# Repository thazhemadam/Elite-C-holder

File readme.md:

# splinterface

splinterface is an MCU holder, intended for use in both standalone and split builds.

## MCU Support

The following footprints are supported by the holder.

* [Elite-C footprint](https://deskthority.net/wiki/Elite-C)
* [nice!nano footprint](https://nicekeyboards.com/docs/nice-nano/pinout-schematic/#pinout)
* [Supermini nrf52840 footprint](https://github.com/joric/nrfmicro/wiki/Alternatives#supermini-nrf52840)

## Features

* [VIK](https://github.com/sadekbaroudi/vik) compliant
* Support for wireless and wired builds (see an example compatibility matrix [below](#compatibility-matrix-with-bastardkb-boards))
* Full-duplex communications support
* Dedicated pin for handedness (optional)
* Dedicated pin for RGB (optional)
* Criss-crossable pins for serial communication

### Wired Builds

* TRRS jack for split communications
* USBLC6-2P6 for ESD protection

### Wireless Builds

* JST-PH connector for connecting a battery
* EG1271 Slide Switches for power switch

## Compatibility Matrix with BastardKB Boards

|                | RGB | Wireless | RGB + Wireless [^1] |
|----------------|:---:|:--------:|:-------------------:|
| Skeletyl       | ✅   | ✅        | ✅                 |
| Charybdis Nano | ✅   | ✅        | ✅                 |
| TBK Mini       | ✅   | ✅ [^2]   | ✅ [^2][^3]        |
| Charybdis Mini | ✅   | ✅ [^2]   | ✅ [^2][^3]        |
| Scylla         | ✅   | ✅ [^3]   | ❌                 |
| Charybdis      | ✅   | ✅ [^3]   | ❌                 |

* Ribbon cable pinout (for the key matrix) compatible with BastardKB's [Dactyl](https://bastardkb.com/dactyls/) and [Charybdis](https://bastardkb.com/charybdis/) series' PCBs.
* Mounting holes are compatible with BastardKB's [Dactyl](https://bastardkb.com/dactyls/) and [Charybdis](https://bastardkb.com/charybdis/) series' cases.

## VIK Certification Card

| Category                | Response           |
| ----------------------- |:------------------:|
| FPC connector           | ✅                 |
| Breakout pins           | ❌                 |
| Supplies: SPI           | ✅                 |
| Supplies: I2C           | ✅                 |
| I2C on main PCB         | ❌                 |
| I2C pull ups            | N/A                |
| Supplies: RGB           | ✅                 |
| Supplies: Extra GPIO 1  | Analog/Digital     |
| Supplies: Extra GPIO 2  | Analog/Digital     |

## License

This work is licensed under a Creative Commons Attribution-NonCommercial-ShareAlike 4.0 International License.

[^1]: Do you even really want to have RGB with a wireless build? Do you, *really*? For obvious battery-related reasons, this is not a recommended build configuration.
[^2]: Requires the `RGB_OR_WL_COL` jumper to be manually soldered appropriately.
[^3]: Requires the `split_hand_or_row` jumper to be manually soldered appropriately. This will reappropriate the dedicated handedness pin. In this case, the handedness will have to be defined in the firmware.

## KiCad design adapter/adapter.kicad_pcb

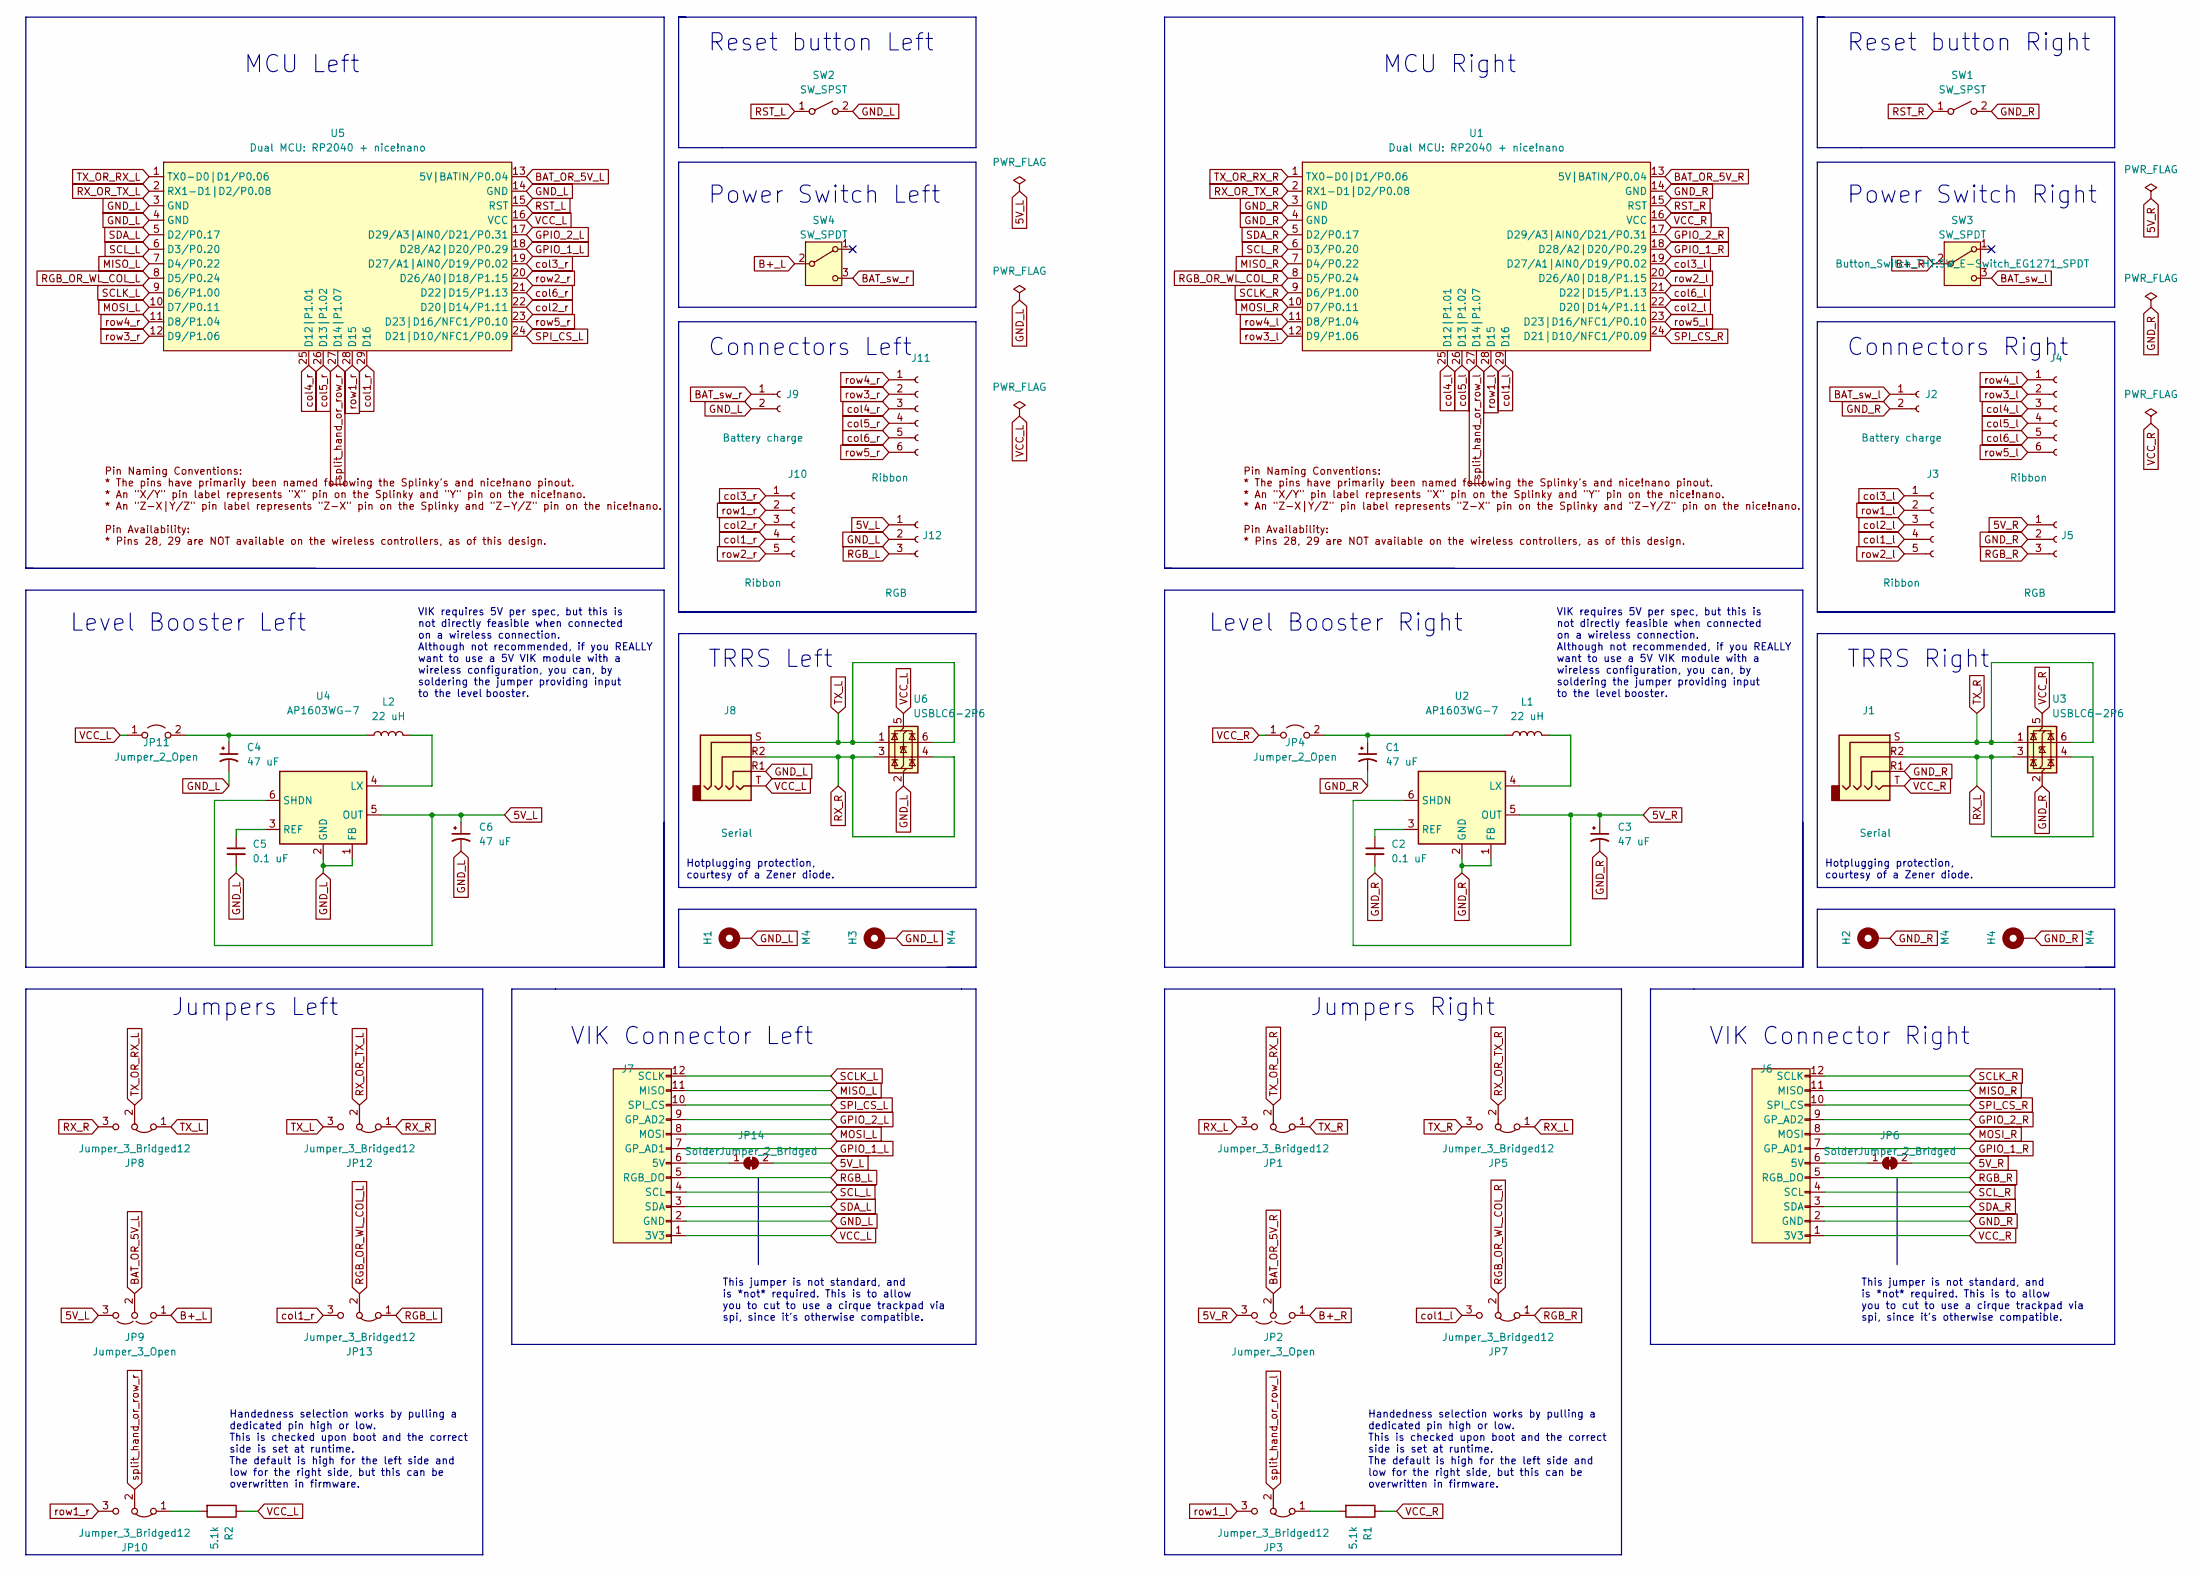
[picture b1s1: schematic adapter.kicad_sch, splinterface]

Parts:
C1, C3, C4, C6: 47 uF; C_0805_2012Metric; LCSC C140782
C2, C5: 0.1 uF; C_0805_2012Metric; LCSC C1525
H1, H2, H3, H4: M4; MountingHole_4mm_Pad_thin
J1, J8: Serial; CON_MJ-4PP-9
J2, J9: Battery charge; JST_PH_B2B-PH-K_1x02_P2.00mm_Vertical
J3, J10: Ribbon; 5_PinHeader
J4, J11: Ribbon; 6_PinHeader
J5, J12: RGB; header1x03
J6, J7: vik-keyboard-connector-horizontal; LCSC C479750
JP1, JP3, JP5, JP7, JP8, JP10, JP12, JP13: Jumper_3_Bridged12; SolderJumper-3_P1.3mm_Bridged12_RoundedPad1.0x1.5mm
JP2, JP9: Jumper_3_Open; SolderJumper-3_P1.3mm_Open_RoundedPad1.0x1.5mm_NumberLabels
JP4, JP11: Jumper_2_Open; SolderJumper-2_P1.3mm_Open_RoundedPad1.0x1.5mm
JP6, JP14: SolderJumper_2_Bridged; SolderJumper-2_P1.3mm_Bridged_RoundedPad1.0x1.5mm
L1, L2: 22 uH; L_0805_2012Metric; LCSC C361669
R1, R2: 5.1k; R_1206_handsolder; JLCPCB BOM 1
SW1, SW2: SW_SPST; PushSwitch
SW3, SW4: SW_SPDT; SW_E-Switch_EG1271_SPDT
U1, U5: Dual MCU: RP2040 + nice!nano; Dual-MCU-rp2040-nice-nano
U2, U4: AP1603WG-7; SOT-23-6; LCSC C192712
U3, U6: USBLC6-2P6; SOT-23-6

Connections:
5V_L: C6.1, J12.1, JP9.3 (B), JP14.2 (B), U4.5 (OUT), U4.6 (SHDN)
5V_R: C3.1, J5.1, JP2.3 (B), JP6.2 (B), U2.5 (OUT), U2.6 (SHDN)
B+_L: JP9.1 (A), SW4.2 (B)
B+_R: JP2.1 (A), SW3.2 (B)
BAT_OR_5V_L: JP9.2 (C), U5.13 (5V|BATIN/P0.04)
BAT_OR_5V_R: JP2.2 (C), U1.13 (5V|BATIN/P0.04)
BAT_sw_l: J2.1, SW3.3 (C)
BAT_sw_r: J9.1, SW4.3 (C)
GND_L: C4.2, C5.2, C6.2, H1.1, H3.1, J7.2 (GND), J8.R1, J9.2, J12.2, SW2.2 (B), U4.1 (FB), U4.2 (GND), U5.3 (GND), U5.4 (GND), U5.14 (GND), U6.2 (GND)
GND_R: C1.2, C2.2, C3.2, H2.1, H4.1, J1.R1, J2.2, J5.2, J6.2 (GND), SW1.2 (B), U1.3 (GND), U1.4 (GND), U1.14 (GND), U2.1 (FB), U2.2 (GND), U3.2 (GND)
GPIO_1_L: J7.7 (GP_AD1), U5.18 (D28/A2|D20/P0.29)
GPIO_1_R: J6.7 (GP_AD1), U1.18 (D28/A2|D20/P0.29)
GPIO_2_L: J7.9 (GP_AD2), U5.17 (D29/A3|AIN0/D21/P0.31)
GPIO_2_R: J6.9 (GP_AD2), U1.17 (D29/A3|AIN0/D21/P0.31)
MISO_L: J7.11 (MISO), U5.7 (D4/P0.22)
MISO_R: J6.11 (MISO), U1.7 (D4/P0.22)
MOSI_L: J7.8 (MOSI), U5.10 (D7/P0.11)
MOSI_R: J6.8 (MOSI), U1.10 (D7/P0.11)
unnamed: J6.6 (5V), JP6.1 (A)
unnamed: J7.6 (5V), JP14.1 (A)
unnamed: JP3.1 (A), R1.2
unnamed: C1.1, JP4.2 (B), L1.1
unnamed: JP10.1 (A), R2.2
unnamed: C4.1, JP11.2 (B), L2.1
unnamed: L1.2, U2.4 (LX)
unnamed: C2.1, U2.3 (REF)
unnamed: L2.2, U4.4 (LX)
unnamed: C5.1, U4.3 (REF)
RGB_L: J7.5 (RGB_DO), J12.3, JP13.1 (A)
RGB_OR_WL_COL_L: JP13.2 (C), U5.8 (D5/P0.24)
RGB_OR_WL_COL_R: JP7.2 (C), U1.8 (D5/P0.24)
RGB_R: J5.3, J6.5 (RGB_DO), JP7.1 (A)
RST_L: SW2.1 (A), U5.15 (RST)
RST_R: SW1.1 (A), U1.15 (RST)
RX_L: J1.R2, JP1.3 (B), JP5.1 (A), U3.3 (I/O2), U3.4 (I/O2)
RX_OR_TX_L: JP12.2 (C), U5.2 (RX1-D1|D2/P0.08)
RX_OR_TX_R: JP5.2 (C), U1.2 (RX1-D1|D2/P0.08)
RX_R: J8.R2, JP8.3 (B), JP12.1 (A), U6.3 (I/O2), U6.4 (I/O2)
SCLK_L: J7.12 (SCLK), U5.9 (D6/P1.00)
SCLK_R: J6.12 (SCLK), U1.9 (D6/P1.00)
SCL_L: J7.4 (SCL), U5.6 (D3/P0.20)
SCL_R: J6.4 (SCL), U1.6 (D3/P0.20)
SDA_L: J7.3 (SDA), U5.5 (D2/P0.17)
SDA_R: J6.3 (SDA), U1.5 (D2/P0.17)
SPI_CS_L: J7.10 (SPI_CS), U5.24 (D21|D10/NFC1/P0.09)
SPI_CS_R: J6.10 (SPI_CS), U1.24 (D21|D10/NFC1/P0.09)
TX_L: J8.S, JP8.1 (A), JP12.3 (B), U6.1 (I/O1), U6.6 (I/O1)
TX_OR_RX_L: JP8.2 (C), U5.1 (TX0-D0|D1/P0.06)
TX_OR_RX_R: JP1.2 (C), U1.1 (TX0-D0|D1/P0.06)
TX_R: J1.S, JP1.1 (A), JP5.3 (B), U3.1 (I/O1), U3.6 (I/O1)
VCC_L: J7.1 (3V3), J8.T, JP11.1 (A), R2.1, U5.16 (VCC), U6.5 (VBUS)
VCC_R: J1.T, J6.1 (3V3), JP4.1 (A), R1.1, U1.16 (VCC), U3.5 (VBUS)
col1_l: J3.4, JP7.3 (B), U1.29 (D16)
col1_r: J10.4, JP13.3 (B), U5.29 (D16)
col2_l: J3.3, U1.22 (D20|D14/P1.11)
col2_r: J10.3, U5.22 (D20|D14/P1.11)
col3_l: J3.1, U1.19 (D27/A1|AIN0/D19/P0.02)
col3_r: J10.1, U5.19 (D27/A1|AIN0/D19/P0.02)
col4_l: J4.3, U1.25 (D12|P1.01)
col4_r: J11.3, U5.25 (D12|P1.01)
col5_l: J4.4, U1.26 (D13|P1.02)
col5_r: J11.4, U5.26 (D13|P1.02)
col6_l: J4.5, U1.21 (D22|D15/P1.13)
col6_r: J11.5, U5.21 (D22|D15/P1.13)
row1_l: J3.2, JP3.3 (B), U1.28 (D15)
row1_r: J10.2, JP10.3 (B), U5.28 (D15)
row2_l: J3.5, U1.20 (D26/A0|D18/P1.15)
row2_r: J10.5, U5.20 (D26/A0|D18/P1.15)
row3_l: J4.2, U1.12 (D9/P1.06)
row3_r: J11.2, U5.12 (D9/P1.06)
row4_l: J4.1, U1.11 (D8/P1.04)
row4_r: J11.1, U5.11 (D8/P1.04)
row5_l: J4.6, U1.23 (D23|D16/NFC1/P0.10)
row5_r: J11.6, U5.23 (D23|D16/NFC1/P0.10)
split_hand_or_row_l: JP3.2 (C), U1.27 (D14|P1.07)
split_hand_or_row_r: JP10.2 (C), U5.27 (D14|P1.07)

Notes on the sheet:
Handedness selection works by pulling a dedicated pin high or low. This is checked upon boot and the correct side is set at runtime. The default is high for the left side and low for the right side, but this can be overwritten in firmware.
Reset button Right
VIK requires 5V per spec, but this is not directly feasible when connected on a wireless connection. Although not recommended, if you REALLY want to use a 5V VIK module with a wireless configuration, you can, by soldering the jumper providing input to the level booster.
TRRS Right
Jumpers Right
Jumpers Left
Connectors Left
Reset button Left
Power Switch Right
Level Booster Left
This jumper is not standard, and is *not* required. This is to allow you to cut to use a cirque trackpad via spi, since it's otherwise compatible.
Power Switch Left
MCU Right
Hotplugging protection, courtesy of a Zener diode.
VIK Connector Left
Connectors Right
VIK Connector Right
MCU Left
Level Booster Right
TRRS Left

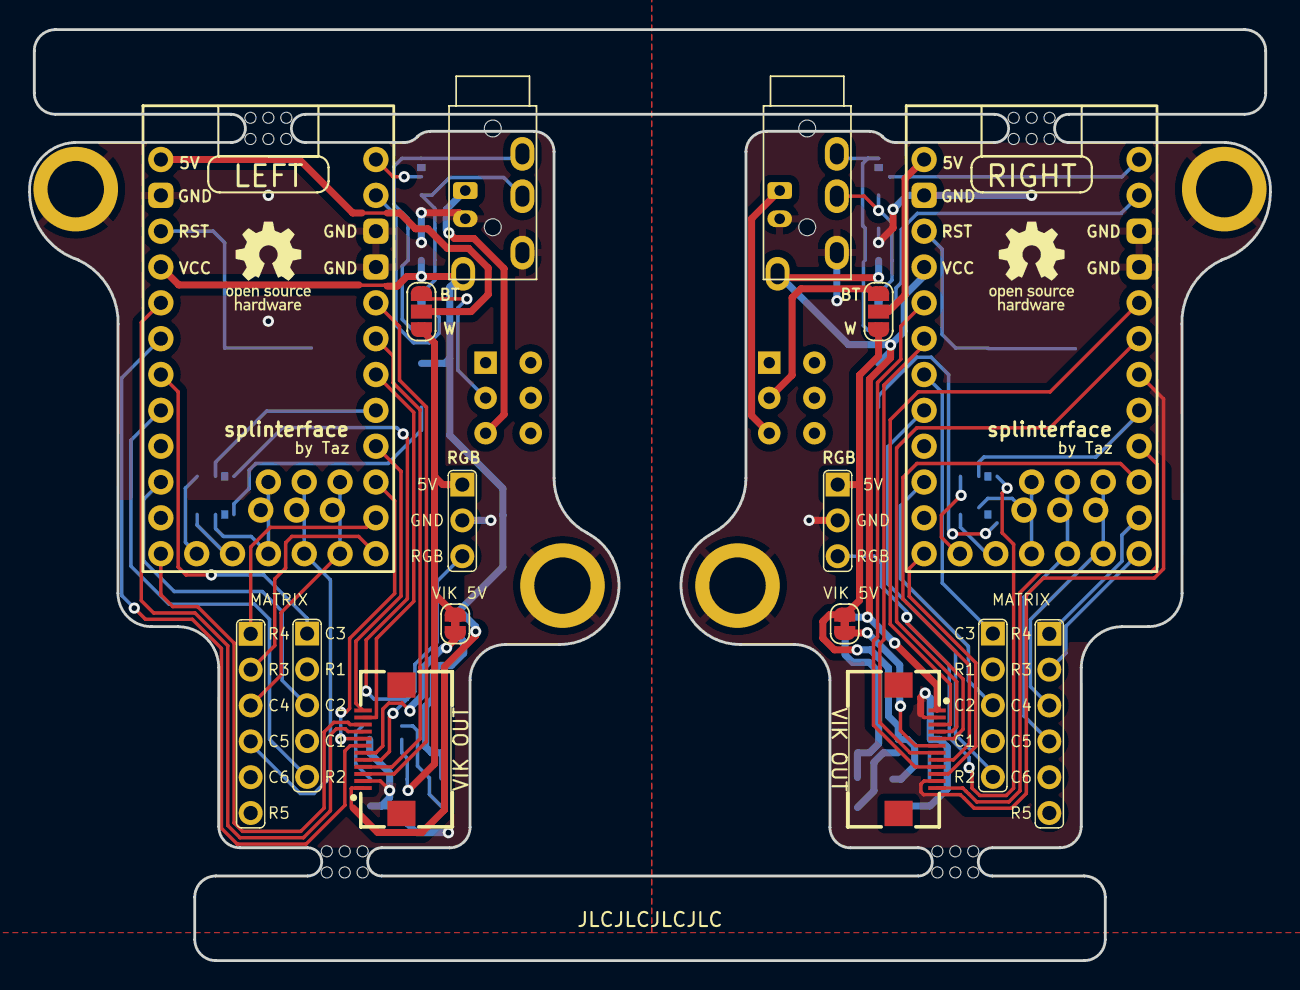
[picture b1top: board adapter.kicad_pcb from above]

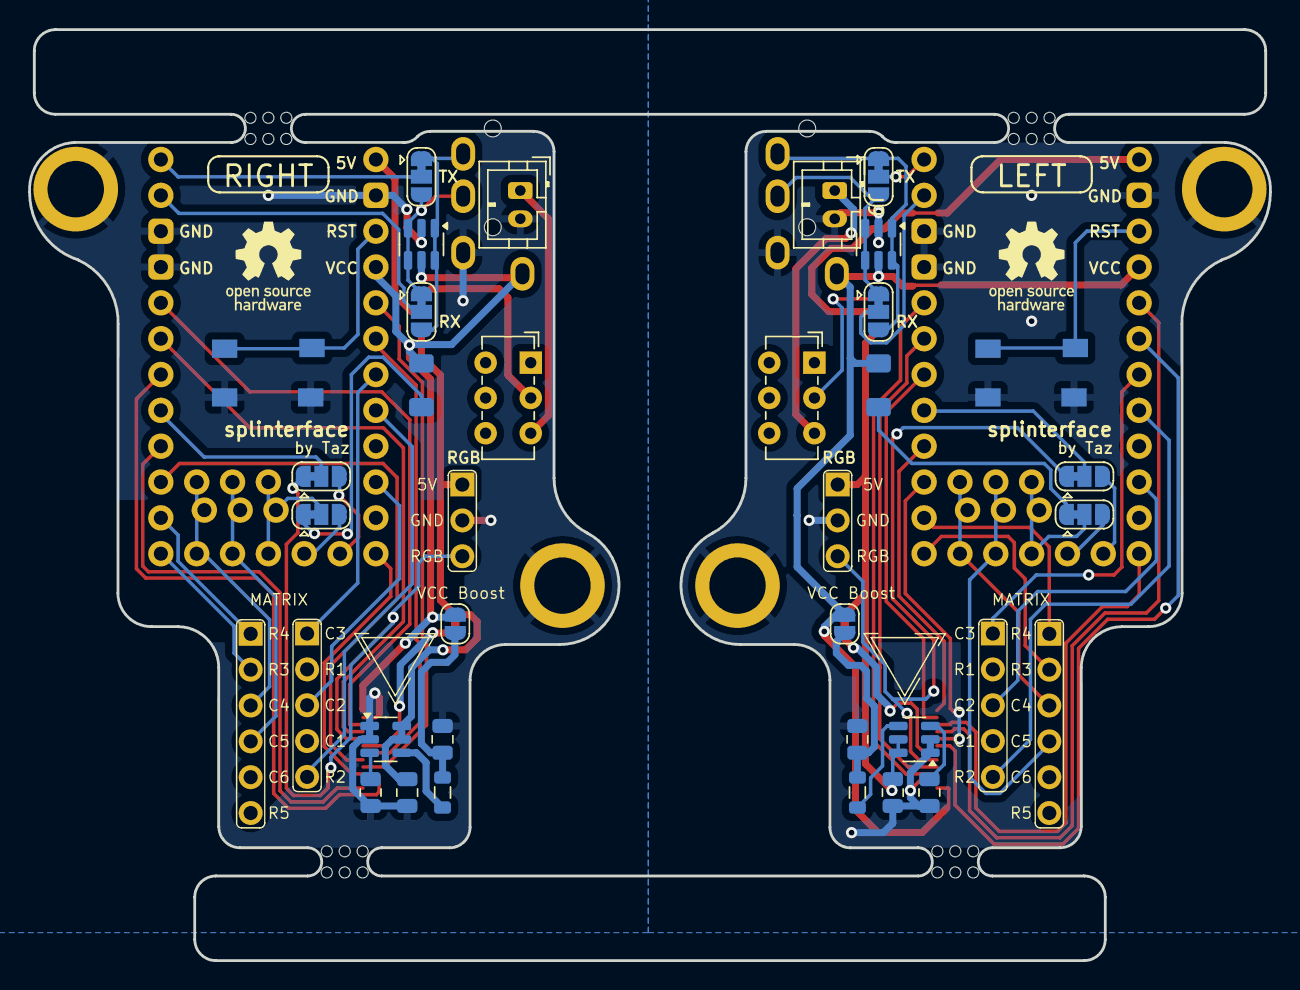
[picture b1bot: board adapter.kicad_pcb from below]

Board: 2 copper layers, 87.9 x 66.0 mm, 54 parts (33 on the bottom side), 76 nets.

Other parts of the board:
H5, H7: Mousebite-Top; mousebites
H6, H8: Mousebite-Bottom; mousebites

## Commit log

2024-05-06 update to kicad v8
2024-05-06 add vik submodule
2024-05-06 add vik libraries
2024-05-06 pcb: remove extraneous drawings
2024-05-06 remove silk screen for trackball breakout
2024-05-06 pcb: remove old `project.db`
2024-05-06 pcb: add marbastlib library
2024-05-06 sch: align items to grid
2024-05-06 sch: add marbastlib-promicroish
2024-05-06 sch: update footprints from library
2024-05-06 sch: update footprints to newer versions
2024-05-06 sch: fix more erc errors
2024-05-06 sch: ignore red herring power output to power output warning
2024-05-06 pcb: refill zone-fills
2024-05-06 sch: use original `Library` elite-c footprint
2024-05-07 remove old library
2024-05-07 libs: add new custom symbol library
2024-05-07 remove old footprint
2024-05-07 docs: update README
2024-05-07 docs: remove old pics and move it around
2024-05-07 refactor(libs): move libs into dedicated library
2024-05-07 libs: add symbol for nice-nano, rp2040 dual byomcu symbol
2024-05-07 libs: fix up dual controller symbol
2024-05-07 libs: remove old elite-c footprint
2024-05-07 libs: add new dual mcu footprint
2024-05-07 pcb: remove all traces
2024-05-08 sch: replace elite-c symbol with dual-rp2040-nicenano symbol
2024-05-08 pcb: remove no longer relevant silkscreen text
2024-05-08 pcb: update the all the footprints to use `library`
2024-05-08 pcb: update footprints from library
2024-05-08 pcb: update some silkscreen
2024-05-08 sch: remove I2C breakouts
2024-05-08 pcb: remove I2C breakouts
2024-05-08 sch: update symbols from library
2024-05-21 pcb(edge-cuts): remove right hand side edge cuts
2024-05-21 pcb(edge-cuts): symmetry!
2024-05-21 pcb(edge-cuts): true symmetry! add rhs too
2024-05-21 pcb: remove all footprints for rhs
2024-05-21 pcb: fix outline drc errors
2024-05-21 pcb: remove middle breakoff partition
2024-05-21 wip vik
2024-05-21 wip: sch: update MCU pins per VIK requirements slightly
2024-05-22 libs(symbol): annotate Splinky pinout instead of elite-c
    Since this is primarily intended for usage with a Splinky and n!n
    pinout anyways, there's no point in still holding on to the Elite-C
    pinout, which is not of much use.
2024-05-22 sch: update schematic from library
2024-05-22 sch: remove I2C pullups from the adapter board
    Remove I2C pullups from the adapter board since it's the responsibility
    of the respective VIK modules (e.g., the VIK trackball sensor PCB) to
    provide I2C pullups.[^1]
    [^1]: https://github.com/sadekbaroudi/vik/blob/96d1c2e098b2f305df47dd9c50749a866b508be5/README.md#module-pcb
2024-05-22 sch: reposition symbols
2024-06-01 sym: fix up symbol
2024-06-01 .gitignore: ignore `#auto_saved_files#`
2024-06-01 sch: remove rhs
2024-06-02 libs(footprint): add nice!nano + supermini footprint
2024-06-07 pcb: remove silkscreen
2024-06-07 pcb: update mcu footprint and adjust edge cuts
2024-06-08 pcb: add VIK FFC connector footprint
2024-08-17 sch: properly assign spi pins
2024-08-17 sch: add vik connector with jumper to cut for cirque
2024-08-17 sch: add jumpers for handling 5v
2024-08-17 sch: add voltage boost circuit
2024-08-17 sch: fix up erc violations and issues
2024-08-19 always have voltage convertor on
2024-08-19 pcb: add 3d model for trrs jack
2024-08-19 pcb: remove random silkscreen
2024-08-19 pcb: position trrs jack perfectly
2024-08-19 libs(holder): add model for splinky with headers
2024-08-19 pcb: use 3d model of splinky for mcu
2024-08-19 pcb: update from schematic
2024-08-19 sch: organize different things
2024-08-29 sch: remove booster circuit
2024-08-29 sch: add jumpers for supporting row 5 and col 6
2024-08-29 sch: add footprints for jumpers
2024-08-29 fix up jumpers
2024-08-29 sch: use zener diode protection circuit with 2.2k resistor
2024-08-29 use 3v3
2024-08-29 sch: add booster circuit
2024-08-29 sch: add jumpers for swapping rx and tx
2024-09-15 sch: fix up level booster circuit
2024-09-15 sch: move (potential) RGB pin to a high freq pin & CS to a low freq pin
2024-09-15 pcb: remove components
2024-09-15 pcb: re-add components
2024-09-15 pcb: position tx and rx jumpers
2024-09-15 pcb: wire up col and row pins
2024-09-15 sch: pull up left-handedness with 3.3v
2024-09-15 pcb: update pcb from schematic
2024-09-15 pcb: wire up spi and i2c
2024-09-15 pcb: remove switch. find nicer place for it
2024-09-15 pcb: define thicc netclass group for pwr traces
2024-09-15 pcb: fix up drc
2024-09-15 pcb: route vik gpios
2024-09-15 pcb: wire up 3v3 rgb and 5v
2024-09-15 pcb: 3d models for headers
2024-09-15 pcb: 3d model for tactile reset switch
2024-09-15 pcb: fix jst-ph orientation
2024-09-15 pcb: connect
2024-09-15 pcb: add handedness pin
2024-09-15 libs(adapter): have solder mask only on one side for MCU
2024-09-15 libs(adapter): properly add 3d model for mcu
2024-09-15 pcb: update footprint from library
2024-09-15 pcb: make level booster circuit components all 0805 size
2024-09-15 pcb: nicer traces
2024-09-15 pcb: fix drc
2024-09-16 sch: replace zener diode + resistor with TVS
2024-09-16 libs(adapter): add symbol for AP1603WG-7 level booster
2024-09-16 sch: add erc exclusions
2024-09-16 sch: use level booster symbol from symbol library
2024-09-16 pcb: use TVS and update pcb from schematic
2024-09-16 pcb: pretty traces
2024-09-16 pcb: add erc exclusions
2024-09-16 sch: update types of jumpers
2024-09-16 pcb: update types of jumpers
2024-09-16 pcb: thick gnd traces
2024-09-16 pcb: thick pwr traces
2024-09-17 pcb: centre vias and switch between the MCU
2024-09-17 sch: add metadata and reorganise
2024-09-17 pcb: realign everything
2024-09-17 sch: copy over schematics for RHS
2024-09-17 sch: different power flags for either side
2024-09-17 sch: add different pwr flags for lhs and rhs
2024-09-17 pcb: use different pwr flags for lhs
2024-09-17 sch: add appropriate erc exclusions
2024-09-17 pcb: update VIK footprint to move silk screen around
2024-09-17 pcb: proper rounded corners on silkscreens
2024-09-17 pcb: realign trrs jack
2024-09-17 pcb: remove unnecessary silk screen
2024-09-18 libs(adapter): add symbol and footprint for 200AWMSP2T2A1M6RE switch
2024-09-18 sch: use vertical JST connector
2024-09-18 sch: use different trrs footprint
2024-09-18 pcb: update
2024-09-18 pcb: fine tune
2024-09-18 pcb: update trrs jack footprint
2024-09-18 libs(adapter): make 200AWMSP2T2A1M6RE footprint symmetric
2024-09-18 pcb: use switch
2024-09-18 pcb: use trrs with no bottom hole
2024-09-18 pcb: use vertical switch
2024-09-18 pcb: free up some space!
2024-09-18 libs(adapter): add 3d model for EG1271 switch
2024-09-18 pcb: update silk screen to have text
2024-09-18 pcb: update silk screen on mcus
2024-09-18 pcb: add osh silk screen
2024-09-18 pcb: add more sikscreen
2024-09-18 pcb: update the trrs footprint
2024-09-27 WIP - RECORD POSITIONS AND REVERT
2024-09-28 libs(adapter): remove top two pads from Dual-MCU footprint
2024-09-28 pcb: start redoing the PCB
2024-09-28 pcb: route
2024-09-28 sch: replace rows and cols for convenient routing
2024-09-28 pcb: centre
2024-09-28 pcb: remove "UPDATE" silkscreen
2024-09-29 libs(adapter): change USB tow PCB silkscreen text to User.comments layer
2024-09-29 libs(adapter): silkscreen fixup
2024-09-29 pcb: add useful silkscreen
2024-09-29 pcb: position booster circuit correctly
2024-09-29 pcb: add good silkscreen
2024-09-29 pcb: clean up courtyard
2024-09-29 pcb: group rhs
2024-09-29 pcb: duplicate for lhs
2024-09-29 pcb: flip lhs
2024-09-29 pcb: ungroup lhs
2024-09-29 pcb: remove lhs traces
2024-09-29 pcb: fix up ground zone for lhs
2024-09-29 pcb: update lhs from schematic
2024-09-29 pcb: place components for lhs correctly
2024-09-29 pcb: start tracing lhs
2024-10-26 pcb: dimensions in millis
2024-10-26 pcb: perfectly symmetrical lhs and rhs
2024-10-26 pcb: exclude violations
2024-10-26 pcb: flip silkscreens correctly
2024-10-26 pcb: add 3d model for switch
2024-10-26 pcb: add VIK silkscreen
2024-10-26 pcb: ignore violations
2024-10-26 pcb: add silkscreen with name
2024-10-26 pcb: swap lhs and rhs sides
2024-10-26 pcb: add to silk lhs
2024-10-26 pcb: fix rx tx silks
2024-10-26 pcb: remove references in silk
2024-10-26 pcb: add "right" and "left" labels
2024-10-26 pcb: bt w labels
2024-10-26 sch: fix names of boxes
2024-10-27 lib: add mousebites footprint
2024-10-27 pcb: add mousebites
2024-10-27 docs: add more info in readme
2024-11-03 pcb: correctly swap L and R labels in schematic
2024-11-03 docs: add footnotes to compatibility matrix
2024-11-03 pcb: rename `serial_x` label to `RX_x`
2024-11-05 silk screens on both sides
2024-11-05 pcb: remove panel
2024-11-05 libs: export and use vik connector footprint
2024-11-05 pcb: LHS only
2024-11-05 pcb: RHS only
2024-11-05 pcb: LHS and RHS
2024-11-05 build: generate production files for LHS
2024-11-05 build: generate production files for RHS
2024-11-05 build: generate production files for panelized design
2024-11-26 libs(adapter): fix GPIO number on footprint, add GPIO number for ADC
2024-11-26 fix: swap col6 and col1
2024-11-26 fix: swap row5 and row1
2024-12-24 fix: swap miso and mosi
2024-12-24 pcb: remove col6, col1, row5, row1 tracks
2024-12-24 fix: swap row1 and col1 for easier routing
2024-12-24 pcb: route jumpers for row1 and col1

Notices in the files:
adapter/adapter.kicad_sch:
Licensed under CERN-OHL-W v2
